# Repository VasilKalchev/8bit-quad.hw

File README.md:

# 8bit-quad

Flight controller **PCB** for a custom-built quadcopter based on the ATmega328
microcontroller. An IMU, an nRF24L01+ radio and four ESC outputs on a 113 mm
octagon shaped to the top plate of an F450 frame.

It was etched at home, populated, flown, and retired. This repository is an
archive of it, not a design anyone is expected to build. [The firmware that
ran on it](https://github.com/VasilKalchev/8bit-quad) is in its own
repository.

<sub>The board on the frame with an FTDI adapter attached. The remote is on
the right, on protoboard. It never had a PCB; what it had to provide is in
<a href="rc/">rc/</a>.</sub>

<table>
<tr>
<td width="50%"></td>
<td width="50%"></td>
</tr>
<tr>
<td align="center"><sub>schematic, click for the PDF</sub></td>
<td align="center"><sub>board</sub></td>
</tr>
</table>

```
fc/          KiCad 10 project, symbols and footprints included
  _export/   schematic and board images
  bom.txt    62 components
rc/          what the remote had to provide
gallery/     photographs
```

Everything the project needs is inside it. There are no dependencies on
installed libraries.

## The board

**The outline** is a 113 mm octagon because the board was originally meant to
*be* the F450's top plate rather than sit on it. A load-bearing flight
controller: the arms bolt through it, every landing is absorbed by the PCB,
the frame's vibration is piped straight into the IMU with nothing in between,
and any crash that would have cracked a plate worth a couple of euros instead
cracks the one part carrying all the electronics. Obvious in hindsight. Also
in foresight, to be fair.

The shape stayed regardless, and the board ended up bolted above the plate
like every other flight controller ever made.

Pin names below are the ones the firmware uses.

**The microcontroller** is an ATmega328P-PU in a DIP-28 socket with a 16 MHz
crystal, programmed over either an AVR ISP header or an FTDI header, with a
restart button next to it.

**The IMU** is an MPU6050 or MPU9250 breakout on I2C. There are two header
footprints for it, 1x8 and 1x5, so either of the two common module shapes
fits. Its interrupt lands on `PD2`. The outline drawn around it is an
anti-vibration plate, drawn when it was still meant to carry the IMU module
and nothing else. It ended up carrying the whole flight controller. So the
vibration problem was understood, and then solved by moving it one level up.

**The radio** is an nRF24L01+ PA/LNA module on hardware SPI, with `CE` on
`PD7`, `CSN` on `PB0` and the interrupt on `PC0`. The firmware's last revision
abandoned it for a PPM receiver, which takes over `PD2`.

**The ESC outputs** are four 3-pin headers labelled by frame position: `TL` on
`PD5`, `TR` on `PB2`, `BL` on `PD6`, `BR` on `PB1`. All four are hardware PWM
outputs, two on timer 0 and two on timer 1. Freeing timer 0 for that is why
the firmware ships its own Arduino core, which moves `millis()` onto timer 2.

**Power** arrived on a JST connector behind a 2 A PPTC and a MOSFET for
reverse polarity, then a 7805 and a TS1117 gave 5 V and 3.3 V. Battery voltage
reached `PC3` through 110k and 20k over 9k1, which the schematic notes as
`Vout = Vbatt * 0.06542056`.

**Indication** is a signal LED on `PC2` and a warning LED on `PC1`, plus two
low side MOSFETs switching an arm-LED header on `PD3` and a lamp header on
`PD4`.

Two measurements from a PicoScope in March 2022, on the built board: the ESC
drive edges rose in 11.2 ns at 5.065 V, and the IMU's I2C lines in 125 ns at
3.542 V.

## Etched at home

There are no gerbers and never were. The copper layers were printed onto
transparency and the board was etched by photoresist, so its rules are
generous: 18 mil clearance, 16 mil minimum track, 0.8 mm minimum drill. There
is [a video of the etching](https://youtu.be/nzKjSb2GAe4).

<sub>Etched, still purple from the photoresist, before drilling. The clearest
record of the artwork that exists.</sub>

> [!NOTE]
> DRC reports three errors, all on `J1P0`, the JST battery connector, whose
> pads and holes break the board's own rules. That is inherent to the
> footprint and predates the KiCad conversion; the board was built and flown
> that way. The rest is cosmetic silkscreen and thermal relief warnings.
> Connectivity is clean, with zero unconnected items once the zones are
> filled.

## History

This board is v2. The first flight controller was an Arduino Nano and an
nRF24L01+ hand wired on protoboard, and it is the reason this one is lettered
`Flight Controller v2.0`.

<sub>v1, the protoboard flight controller this board replaced. Its IMU
module is missing here.</sub>

It was drawn in Eagle. Autodesk stopped developing standalone Eagle in 2024
and folded it into Fusion, so the design was converted to KiCad in 2026. The
original Eagle files are in the first commit of this repository and nowhere
else.

## Licence

Copyright Vasil Kalchev 2017

Licensed under CERN-OHL-P v2 or later. You may redistribute and modify this
source and make products using it under the terms of the
[CERN-OHL-P v2](https://ohwr.org/cern_ohl_p_v2.txt). This source is
distributed WITHOUT ANY EXPRESS OR IMPLIED WARRANTY, INCLUDING OF
MERCHANTABILITY, SATISFACTORY QUALITY AND FITNESS FOR A PARTICULAR PURPOSE.
Please see the CERN-OHL-P v2 for applicable conditions.

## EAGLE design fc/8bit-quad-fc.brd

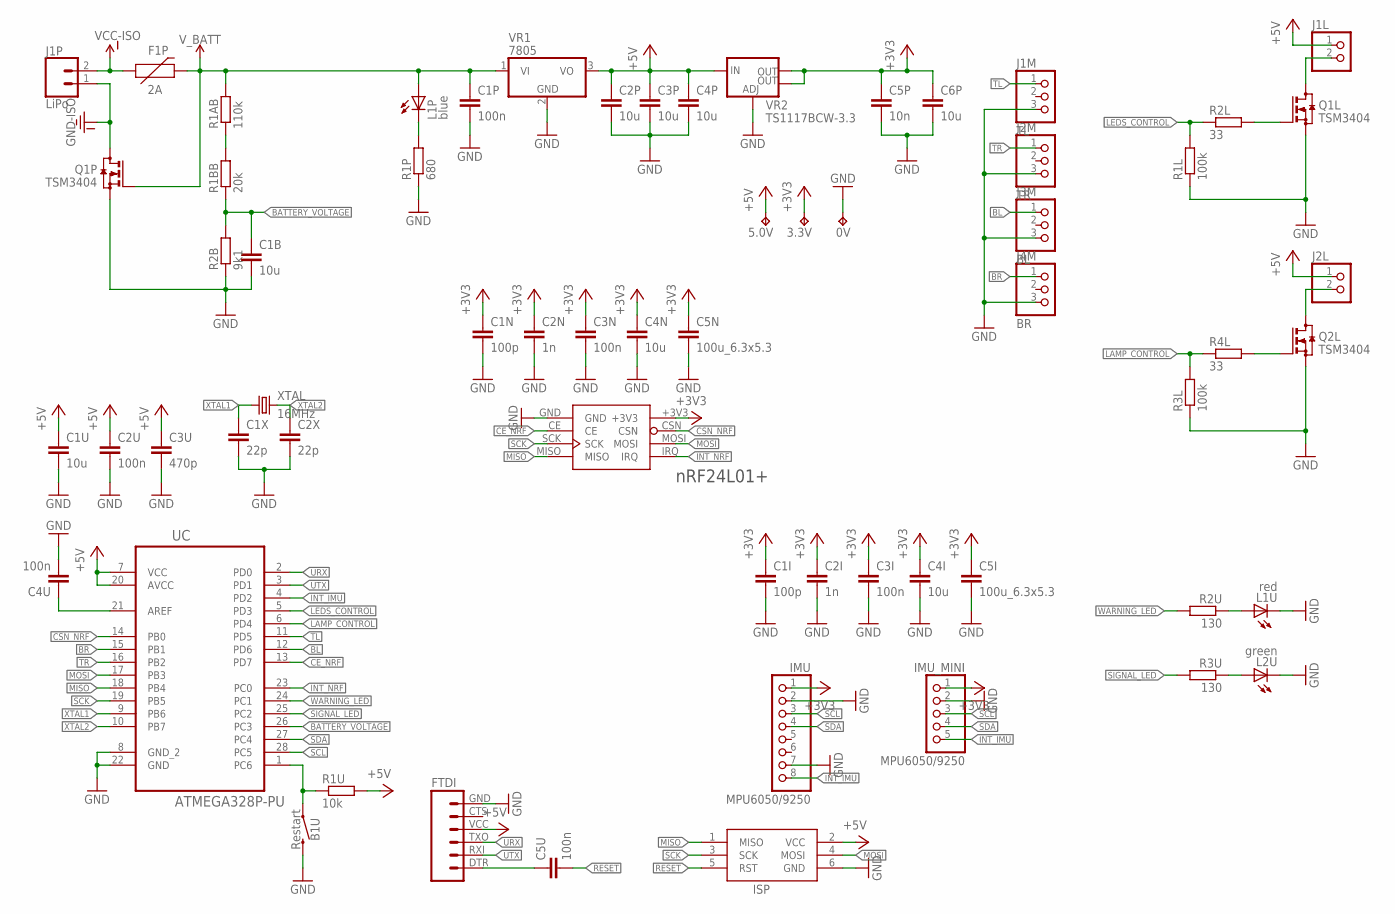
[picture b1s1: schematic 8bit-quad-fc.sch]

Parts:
0V, 3.3V, 5.0V: TPTP10SQ; TP10SQ
B1U: Restart; TACTILE_SWITCH_PTH_6.0MM
C1B, C1U, C2P, C3P, C4I, C4N, C4P, C6P: 10u; C1206
C1I, C1N: 100p; C1206
C1P, C2U, C3I, C3N, C4U, C5U: 100n; C1206
C1X, C2X: 22p; C1206
C2I, C2N: 1n; C1206
C3U: 470p; C1206
C5I, C5N: 100u_6.3x5.3; C3225
C5P: 10n; C1206
F1P: 2A; 1206
FTDI: FTDI_BASICPTH; FTDI_BASIC
IMU: MPU6050/9250; 1X08
IMU_MINI: MPU6050/9250; 1X05
ISP: AVRISP-6; AVRISP
J1L, J2L: PINHD-1X2/90; 1X02/90
J1M: TL; 1X03/90
J1P: LiPo; JST-2-PTH
J2M: TR; 1X03/90
J3M: BL; 1X03/90
J4M: BR; 1X03/90
L1P: blue; 1206
L1U: red; 1206
L2U: green; 1206
NRF24L01+: nRF24L01+; NRF24L01+_PA_LNA_SMD
Q1L, Q1P, Q2L: TSM3404; SOT23
R1AB: 110k; R1206
R1BB: 20k; R1206
R1L, R3L: 100k; R1206
R1P: 680; R1206
R1U: 10k; R1206
R2B: 9k1; R1206
R2L, R4L: 33; R1206
R2U, R3U: 130; R1206
UC: ATMEGA328P-PU; DIP254P762X457-28
VR1: 7805; TO220V
VR2: TS1117BCW-3.3; SOT223
XTAL: 16MHz; HC49/S

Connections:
+3V3: 3.3V.TP, C1I.1, C1N.1, C2I.1, C2N.1, C3I.1, C3N.1, C4I.1, C4N.1, C5I.1, C5N.1, C5P.1, C6P.1, IMU.1, IMU_MINI.1, NRF24L01+.+3V3, VR2.2 (OUT), VR2.4 (OUT)
+5V: 5.0V.TP, C1U.1, C2P.1, C2U.1, C3P.1, C3U.1, C4P.1, FTDI.VCC (4), ISP.2 (VCC), J1L.1, J2L.1, R1U.2, UC.7 (VCC), UC.20 (AVCC), VR1.3 (VO), VR2.3 (IN)
BATTERY_VOLTAGE: C1B.1, R1BB.1, R2B.2, UC.26 (PC3)
BL: J3M.1, UC.12 (PD6)
BR: J4M.1, UC.15 (PB1)
CE_NRF: NRF24L01+.CE, UC.13 (PD7)
CSN_NRF: NRF24L01+.CSN, UC.14 (PB0)
GND: 0V.TP, B1U.3 (2), C1B.2, C1I.2, C1N.2, C1P.2, C1U.2, C1X.2, C2I.2, C2N.2, C2P.2, C2U.2, C2X.2, C3I.2, C3N.2, C3P.2, C3U.2, C4I.2, C4N.2, C4P.2, C4U.2, C5I.2, C5N.2, C5P.2, C6P.2, FTDI.GND (6), IMU.2, IMU.7, IMU_MINI.2, ISP.6 (GND), J1M.3, J2M.3, J3M.3, J4M.3, L1U.C, L2U.C, NRF24L01+.GND, Q1L.2 (S), Q1P.2 (S), Q2L.2 (S), R1L.1, R1P.1, R2B.1, R3L.1, UC.8 (GND_2), UC.22 (GND), VR1.2 (GND), VR2.1 (ADJ)
GND-ISO: J1P.1, Q1P.3 (D)
INT_IMU: IMU.8, IMU_MINI.5, UC.4 (PD2)
INT_NRF: NRF24L01+.IRQ, UC.23 (PC0)
LAMP_CONTROL: R3L.2, R4L.1, UC.6 (PD4)
LAMP_SINK: J2L.2, Q2L.3 (D)
LEDS_CONTROL: R1L.2, R2L.1, UC.5 (PD3)
LEDS_SINK: J1L.2, Q1L.3 (D)
MISO: ISP.1 (MISO), NRF24L01+.MISO, UC.18 (PB4)
MOSI: ISP.4 (MOSI), NRF24L01+.MOSI, UC.17 (PB3)
unnamed: L2U.A, R3U.1
unnamed: R1AB.1, R1BB.2
unnamed: L1U.A, R2U.1
unnamed: Q1L.1 (G), R2L.2
unnamed: Q2L.1 (G), R4L.2
unnamed: L1P.C, R1P.2
unnamed: C4U.1, UC.21 (AREF)
unnamed: C5U.1, FTDI.DTR (1)
RESET: B1U.1, C5U.2, ISP.5 (RST), R1U.1, UC.1 (PC6)
SCK: ISP.3 (SCK), NRF24L01+.SCK, UC.19 (PB5)
SCL: IMU.3, IMU_MINI.3, UC.28 (PC5)
SDA: IMU.4, IMU_MINI.4, UC.27 (PC4)
SIGNAL_LED: R3U.2, UC.25 (PC2)
TL: J1M.1, UC.11 (PD5)
TR: J2M.1, UC.16 (PB2)
URX: FTDI.TXO (3), UC.2 (PD0)
UTX: FTDI.RXI (2), UC.3 (PD1)
VCC-ISO: F1P.1, J1P.2
V_BATT: C1P.1, F1P.2, L1P.A, Q1P.1 (G), R1AB.2, VR1.1 (VI)
WARNING_LED: R2U.2, UC.24 (PC1)
XTAL1: C1X.1, UC.9 (PB6), XTAL.1
XTAL2: C2X.1, UC.10 (PB7), XTAL.2

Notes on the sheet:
nRF24L01+

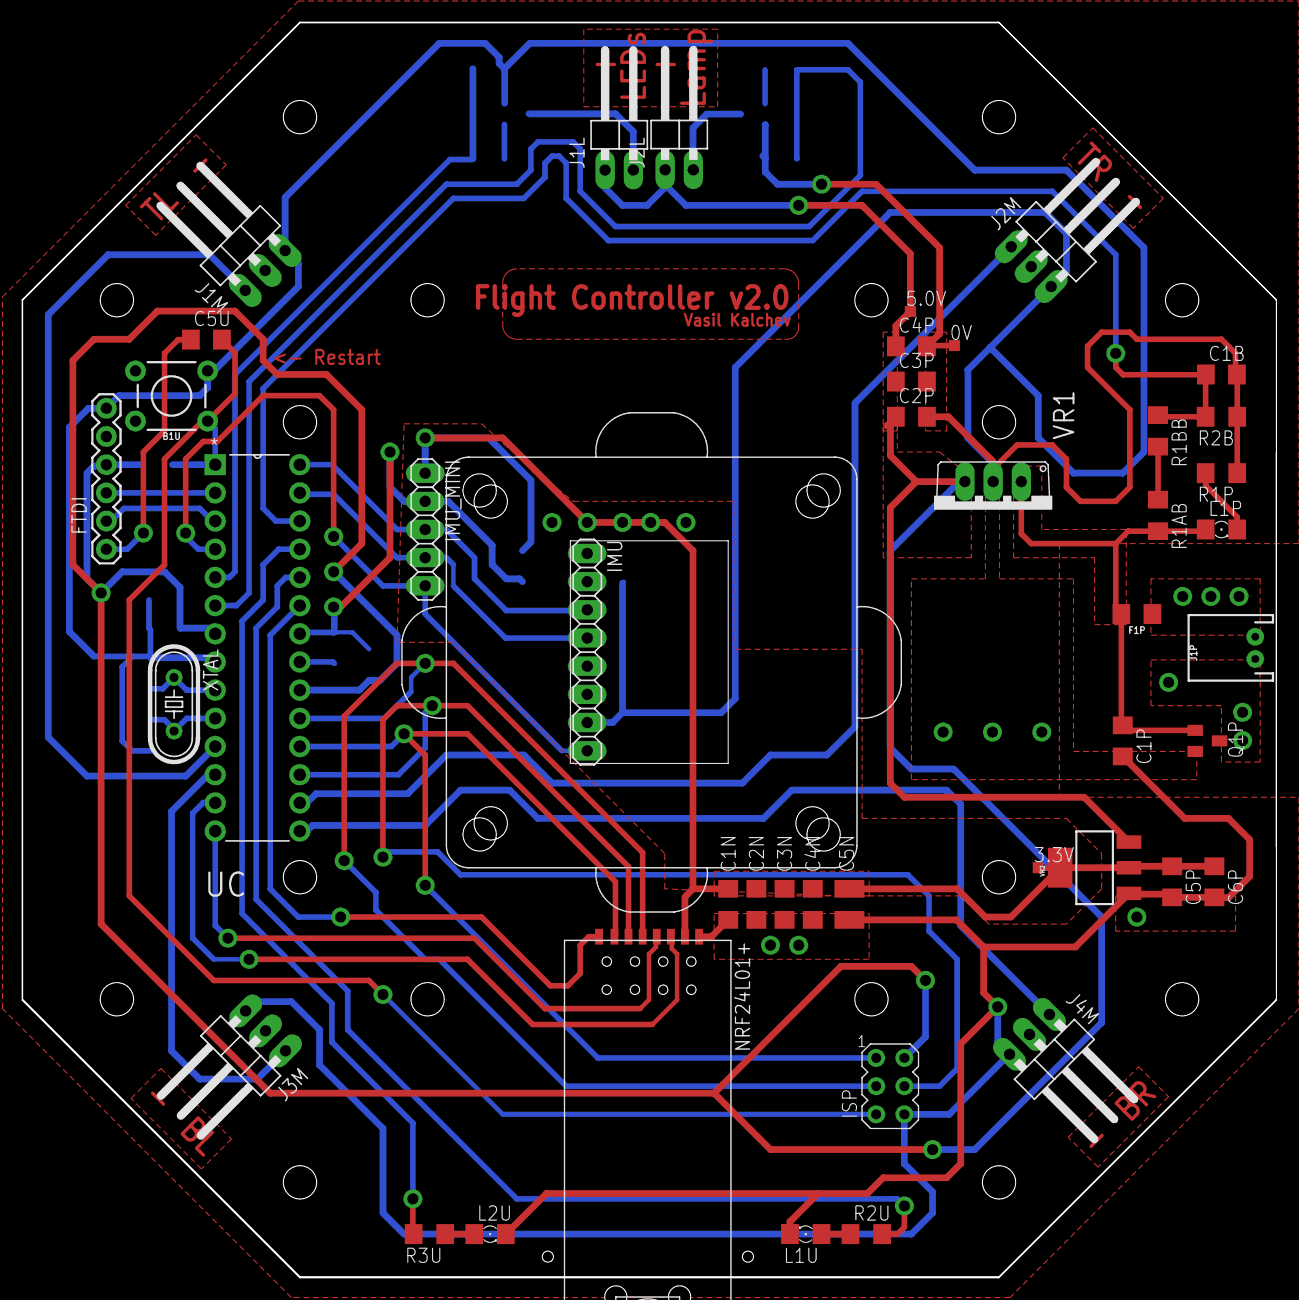
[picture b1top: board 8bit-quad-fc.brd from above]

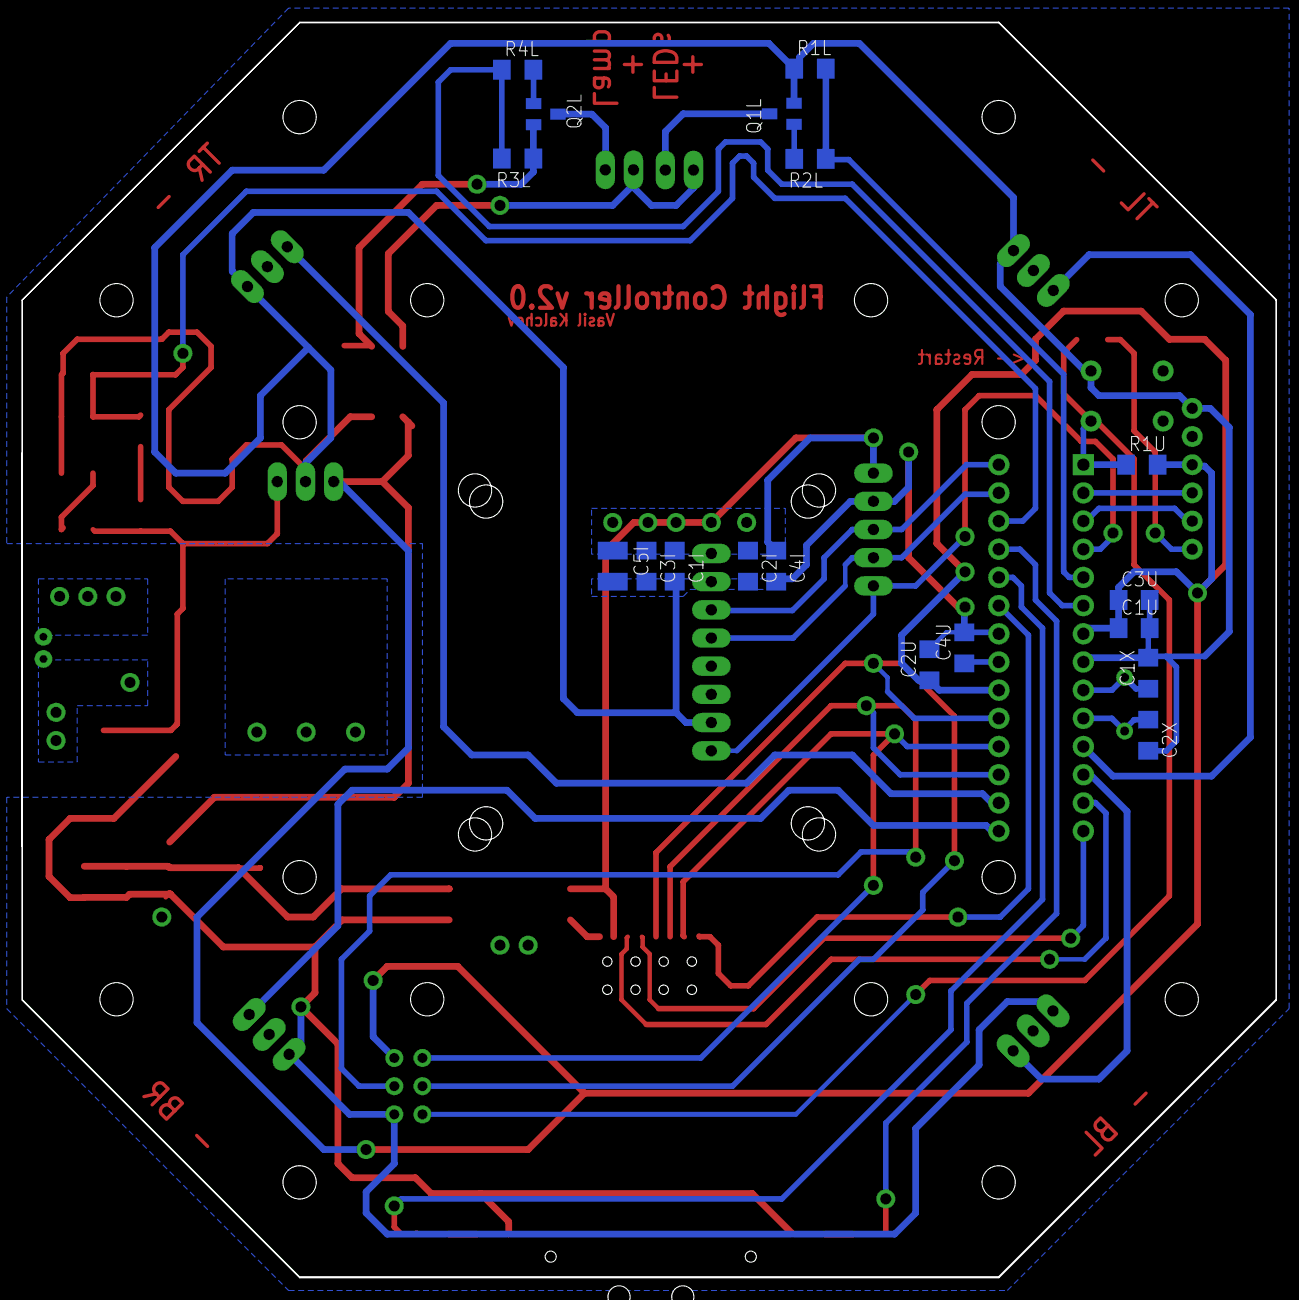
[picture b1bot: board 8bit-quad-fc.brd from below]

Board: 2 copper layers, 113.0 x 113.2 mm, 64 parts (18 on the bottom side), 39 nets.

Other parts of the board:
U$2: F450_TOP_PLATE
U$3: ANTI-VIBRATION_PLATE

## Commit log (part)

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2017-12-04 Flight controller board, drawn in Eagle and etched at home
    Two layer, 113 mm octagon cut to sit on the top plate of an F450 frame.
    ATmega328P at 16 MHz with an nRF24L01+ PA/LNA module, an MPU6050 or MPU9250
    on either an 8 pin or a 5 pin header, and four 3 pin ESC outputs labelled by
    frame position.
    Power comes in on a JST connector behind a 2 A PPTC and a MOSFET for reverse
    polarity, then a 7805 and a TS1117 for 5 V and 3.3 V. Battery voltage reaches
2018-03-07 Photographs of the etched board
    20180117_133531 is the populated board on the frame, powered, with an FTDI
    adapter attached and the nRF24 and IMU modules seated.
    20180307_234316 is a bare board straight on, still purple from the
    photoresist, before drilling and populating. It is the clearest surviving
    record of the artwork: the octagon, the TL, TR, BL and BR motor labels, the
    Restart, LEDs and Lamp legends, and the title block reading Flight Controller

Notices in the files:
parts and their libraries:
SparkFun-Fuses: Licensing: Creative Commons ShareAlike 4.0 International - https://creativecommons.org/licenses/by-sa/4.0
